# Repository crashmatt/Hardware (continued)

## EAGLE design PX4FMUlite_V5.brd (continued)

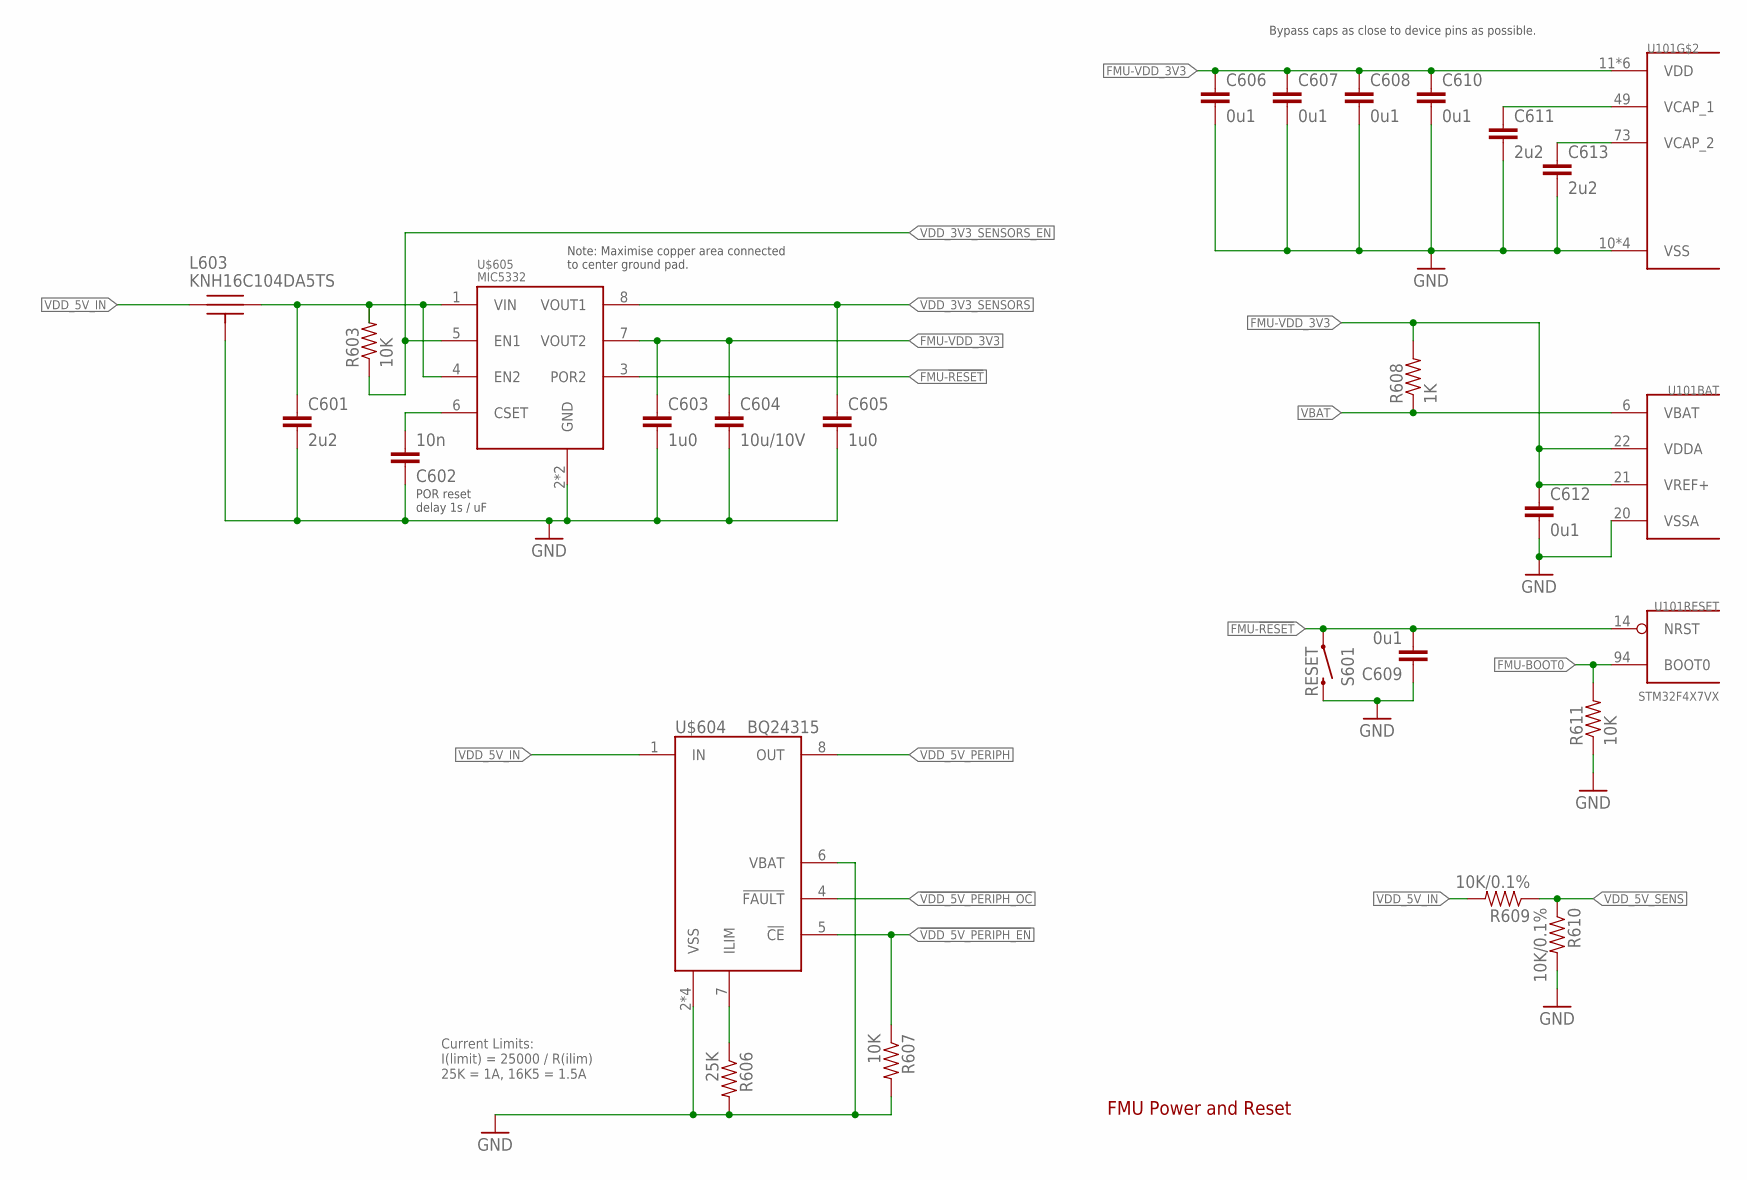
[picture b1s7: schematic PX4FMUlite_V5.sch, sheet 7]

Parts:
C601, C611, C613: 2u2; 0603-CAP; PARTNO C1608Y5V1C225Z
C602: 10n; 0402-CAP; PARTNO CC0402KRX7R7BB103
C603, C605: 1u0; 0603-CAP; PARTNO CC0603ZRY5V7BB105
C604: 10u/10V; 0805-CAP; PARTNO CC0805ZKY5V6BB106
C606, C607, C608, C609, C610, C612: 0u1; 0402-CAP; PARTNO CC0402ZRY5V7BB104
L603: KNH16C104DA5TS; KYOCERA-KNH16-DA; PARTNO KNH16C104DA5TS
R603, R607, R611: 10K; 0402-RES; PARTNO RC0402FR-0710KL
R606: 25K; 0402-RES; PARTNO RMCF0402FT25K5
R608: 1K; 0402-RES; PARTNO RC0402FR-071KL
R609, R610: 10K/0.1%; 0402-RES; PARTNO ERA-2AEB103X
S601: RESET; EVQP7J01K; PARTNO EVQP7J01K
U101: STM32F4X7VX; TQFP100; PARTNO STM32F427VI
U$604: BQ24315; QFN8-DSG; PARTNO BQ24315DSGR
U$605: MIC5332; MLF-8-EPAD; PARTNO MIC5332-SSYMT

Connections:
!VDD_5V_PERIPH_EN: R607.P$1 (1), U$604.5 (!CE); also elsewhere on the board
!VDD_5V_PERIPH_OC: U$604.4 (!FAULT); also elsewhere on the board
FMU-!RESET: C609.P$2 (2), S601.A1 (1), U101.14 (NRST), U$605.3 (POR2); also elsewhere on the board
FMU-BOOT0: R611.P$2 (2), U101.94 (BOOT0); also elsewhere on the board
FMU-VDD_3V3: C603.P$1 (1), C604.P$1 (1), C606.P$1 (1), C607.P$1 (1), C608.P$1 (1), C610.P$1 (1), C612.P$1 (1), R608.P$2 (2), U101.11 (VDD), U101.19 (VDD), U101.21 (VREF+), U101.22 (VDDA), U101.28 (VDD), U101.50 (VDD), U101.75 (VDD), U101.100 (VDD), U$605.7 (VOUT2); also elsewhere on the board
FMU-VDD_5V5: C601.P$1 (1), L603.P$2, R603.P$2 (2), U$605.1 (VIN), U$605.4 (EN2)
GNDX: C601.P$2 (2), C602.P$1 (1), C603.P$2 (2), C604.P$2 (2), C605.P$2 (2), C606.P$2 (2), C607.P$2 (2), C608.P$2 (2), C609.P$1 (1), C610.P$2 (2), C611.P$2 (2), C612.P$2 (2), C613.P$2 (2), L603.P$3, L603.P$4, L603.P$5, R606.P$2 (2), R607.P$2 (2), R610.P$2 (2), R611.P$1 (1), S601.B3 (2), U101.10 (VSS), U101.20 (VSSA), U101.27 (VSS), U101.74 (VSS), U101.99 (VSS), U$604.2 (VSS), U$604.6 (VBAT), U$604.GND (VSS), U$604.P$2 (VSS), U$604.P$3 (VSS), U$605.2 (GND), U$605.GND; also elsewhere on the board
unnamed: C613.P$1 (1), U101.73 (VCAP_2)
unnamed: C602.P$2 (2), U$605.6 (CSET)
unnamed: C611.P$1 (1), U101.49 (VCAP_1)
unnamed: R606.P$1 (1), U$604.7 (ILIM)
VBAT: R608.P$1 (1), U101.6 (VBAT)
VDD_3V3_SENSORS: C605.P$1 (1), U$605.8 (VOUT1); also elsewhere on the board
VDD_3V3_SENSORS_EN: R603.P$1 (1), U$605.5 (EN1); also elsewhere on the board
VDD_5V_IN: L603.P$1, R609.P$2 (2), U$604.1 (IN); also elsewhere on the board
VDD_5V_PERIPH: U$604.8 (OUT); also elsewhere on the board
VDD_5V_SENS: R609.P$1 (1), R610.P$1 (1); also elsewhere on the board

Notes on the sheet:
FMU Power and Reset
Bypass caps as close to device pins as possible.
Note: Maximise copper area connected to center ground pad.
POR reset delay 1s / uF
Current Limits: I(limit) = 25000 / R(ilim) 25K = 1A, 16K5 = 1.5A

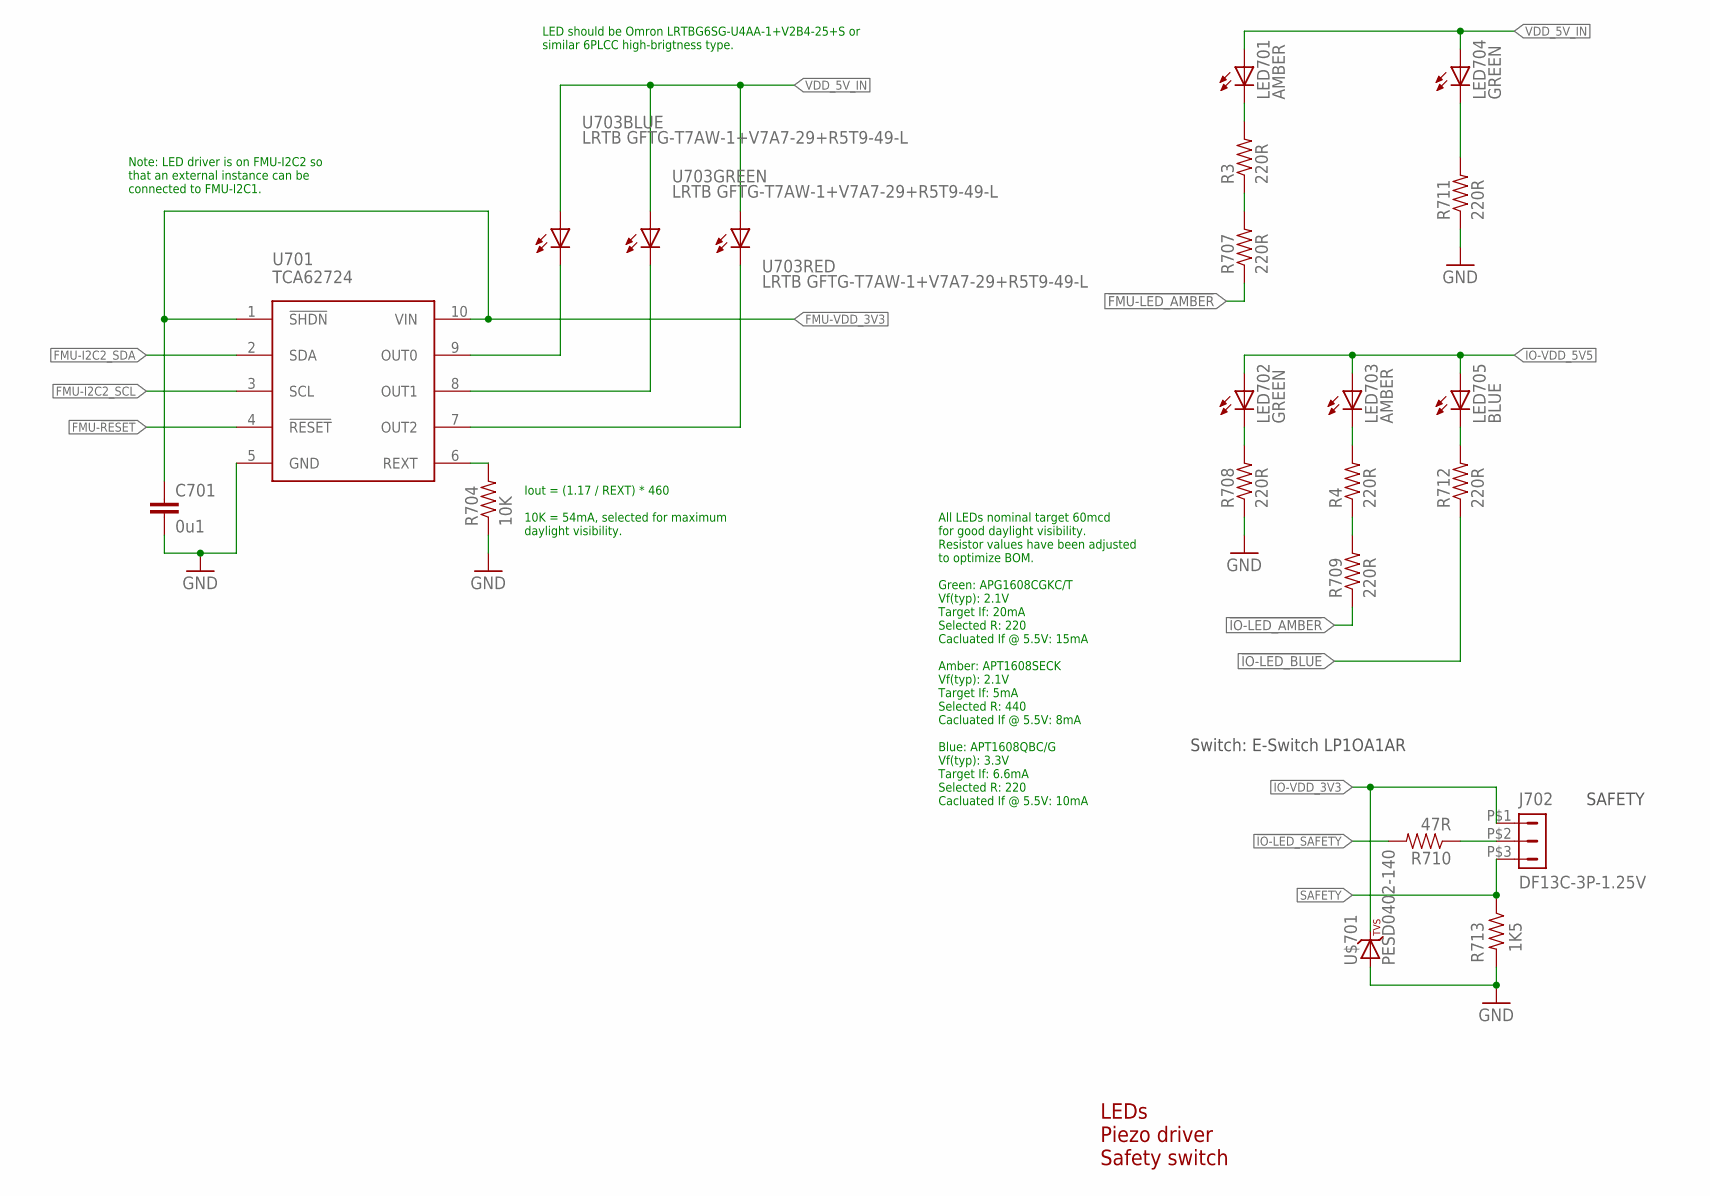
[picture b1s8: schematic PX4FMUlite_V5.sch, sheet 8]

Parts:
C701: 0u1; 0402-CAP; PARTNO CC0402ZRY5V7BB104
J702: DF13C-3P-1.25V; PARTNO DF13C-3P-1.25V(20)
LED701, LED703: AMBER; 0603-LED; PARTNO APTD1608SECK
LED702, LED704: GREEN; 0603-LED; PARTNO APTD1608CGCK
LED705: BLUE; 0603-LED; PARTNO APTD1608QBC/D
R3, R4, R707, R708, R709, R711, R712: 220R; 0402-RES; PARTNO RC0402FR-07220RL
R704: 10K; 0402-RES; PARTNO RC0402FR-0710KL
R710: 47R; 0402-RES; PARTNO RC0402JR-0747RL
R713: 1K5; 0402-RES; PARTNO RC0402FR-071K5L
U701: TCA62724FMG; SON10; PARTNO TCA62724FMG
U703: LRTB GFTG-T7AW-1+V7A7-29+R5T9-49-L; 6-PLCC; PARTNO LRTB GFTG-T7AW-1+V7A7-29+R5T9-49-L
U$701: PESD0402-140; 0402-TVS; PARTNO PESD0402-140

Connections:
!FMU-LED_AMBER: R707.P$1 (1); also elsewhere on the board
!IO-LED_AMBER: R709.P$1 (1)
!IO-LED_BLUE: R712.P$1 (1)
!IO-LED_SAFETY: R710.P$2 (2)
FMU-!RESET: U701.4 (!RESET); also elsewhere on the board
FMU-I2C2_SCL: U701.3 (SCL); also elsewhere on the board
FMU-I2C2_SDA: U701.2 (SDA); also elsewhere on the board
FMU-VDD_3V3: C701.P$1 (1), U701.1 (!SHDN), U701.10 (VIN); also elsewhere on the board
GNDX: C701.P$2 (2), R704.P$1 (1), R708.P$1 (1), R711.P$1 (1), R713.P$2 (2), U701.5 (GND), U$701.A; also elsewhere on the board
IO-VDD_3V3: J702.P$1 (1), U$701.C; also elsewhere on the board
IO-VDD_5V5: LED702.A, LED703.A, LED705.A; also elsewhere on the board
unnamed: LED704.C, R711.P$2 (2)
unnamed: LED705.C, R712.P$2 (2)
unnamed: R3.P$1 (1), R707.P$2 (2)
unnamed: LED701.C, R3.P$2 (2)
unnamed: LED702.C, R708.P$2 (2)
unnamed: R4.P$1 (1), R709.P$2 (2)
unnamed: LED703.C, R4.P$2 (2)
unnamed: J702.P$2 (2), R710.P$1 (1)
unnamed: R704.P$2 (2), U701.6 (REXT)
RGB_LED_3: U701.9 (OUT0), U703.C1 (C)
RGB_LED_4: U701.8 (OUT1), U703.C2 (C)
RGB_LED_14: U701.7 (OUT2), U703.C3 (C)
SAFETY: J702.P$3 (3), R713.P$1 (1)
VDD_5V_IN: LED701.A, LED704.A, U703.A1 (A), U703.A2 (A), U703.A3 (A); also elsewhere on the board

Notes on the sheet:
LEDs Piezo driver Safety switch
Switch: E-Switch LP1OA1AR
SAFETY
LED should be Omron LRTBG6SG-U4AA-1+V2B4-25+S or similar 6PLCC high-brigtness type.
Iout = (1.17 / REXT) * 460 10K = 54mA, selected for maximum daylight visibility.
Note: LED driver is on FMU-I2C2 so that an external instance can be connected to FMU-I2C1.
All LEDs nominal target 60mcd for good daylight visibility. Resistor values have been adjusted to optimize BOM. Green: APG1608CGKC/T Vf(typ): 2.1V Target If: 20mA Selected R: 220 Cacluated If @ 5.5V: 15mA Amber: APT1608SECK Vf(typ): 2.1V Target If: 5mA Selected R: 440 Cacluated If @ 5.5V: 8mA Blue: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

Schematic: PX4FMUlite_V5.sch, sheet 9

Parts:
J801: JST-ZH-3; JST-ZH-SMT-VERTICAL; PARTNO B3B-ZR-SM4-TF (LF)(SN)(P)
JX801: HEADER-3X1BOARDEDGE-SHORT; HEADER_3X01_SMD_H_BOARD_EDGE_SHORT
U$801: PESD0402-140; 0402-TVS; PARTNO PESD0402-140

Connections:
GNDX: J801.P$2, JX801.3 (GND), U$801.A; also elsewhere on the board
IO-USART1_RX: J801.P$3, JX801.2 (+5V)
IO-USART1_TX: JX801.1 (PPM); also elsewhere on the board
VDD_3V3_SPEKTRUM: J801.P$1, U$801.C; also elsewhere on the board

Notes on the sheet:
IO SoC Ports Spektrum/DSM port
IO_SERIAL1
Spektrum/DSM
Timer allocation: PA0: TIM2_CH1: IO-CH1 PA1: TIM2_CH2: IO-CH2 PB8: TIM4_CH3: IO-CH3 PB9: TIM4_CH4: IO-CH4 PA6: TIM3_CH1: IO-CH5 PA7: TIM3_CH2: IO-CH6 PB0: TIM3_CH3: IO-CH7 PB1: TIM3_CH4: IO-CH8 PA8: TIM1_CH1: PPM_IN PA11: TIM1_CH4: RSSI_IN

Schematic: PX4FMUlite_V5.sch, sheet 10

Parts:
C901, C902: 0u1; 0402-CAP; PARTNO CC0402ZRY5V7BB104
D1: MSS1P4-M3; MICROSMP; PARTNO MSS1P4-M3/89A
J901: HEADER-3X163X16RA; 3X16RA
L901: KNH16C104DA5TS; KYOCERA-KNH16-DA; PARTNO KNH16C104DA5TS
R901: 10K; 0402-RES; PARTNO RC0402FR-0710KL
R902, R903, R904, R909, R910, R911, R912, R913: 220R; 0402-RES; PARTNO RC0402FR-07220RL
R918, R919, R922: 10K/0.1%; 0402-RES; PARTNO ERA-2AEB103X
U901: TXS0108QFN20; QFN20-RGY; PARTNO TXS0108ERGYR
U903: 74LVC2G240; TSSOP8_SOT505-2; PARTNO 74LVC2G240DP,125
U$6, U$901, U$902: PESD0402-140; 0402-TVS; PARTNO PESD0402-140

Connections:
!SBUS_OUTPUT_EN: U903.7 (!2OE)
FMU-CH1: U901.7 (A6); also elsewhere on the board
FMU-CH1-PROT: J901.46, R913.P$2 (2)
FMU-CH2: U901.6 (A5); also elsewhere on the board
FMU-CH3: U901.5 (A4); also elsewhere on the board
FMU-CH4: U901.4 (A3); also elsewhere on the board
FMU-CH5: U901.3 (A2); also elsewhere on the board
FMU-CH6: U901.1 (A1); also elsewhere on the board
FMU-CH6-PROT: J901.31, R902.P$2 (2)
FMU-VDD_3V3: C902.P$1 (1), U901.2 (VCCA), U901.10 (OE), U901.19 (VCCB); also elsewhere on the board
GNDX: C901.P$2 (2), C902.P$2 (2), J901.3, J901.6, J901.9, J901.12, J901.15, J901.18, J901.21, J901.24, J901.27, J901.30, J901.33, J901.36, J901.39, J901.42, J901.45, J901.48, L901.P$3, L901.P$4, L901.P$5, R919.P$1 (1), U901.11 (GND), U903.1 (!1OE), U903.4 (GND), U$6.A, U$901.A, U$902.A; also elsewhere on the board
IO-VDD_3V3: C901.P$1 (1), U903.8 (VCC); also elsewhere on the board
IO-VDD_5V5: J901.2; also elsewhere on the board
unnamed: R918.P$2 (2), R922.P$1 (1)
unnamed: R901.P$2 (2), R910.P$1 (1), U903.3 (2Y), U$902.C
unnamed: R902.P$1 (1), U901.20 (B1)
unnamed: R911.P$1 (1), U901.18 (B2)
unnamed: R903.P$1 (1), U901.17 (B3)
unnamed: R912.P$1 (1), U901.16 (B4)
unnamed: R904.P$1 (1), U901.15 (B5)
unnamed: R913.P$1 (1), U901.14 (B6)
unnamed: J901.34, R911.P$2 (2)
unnamed: J901.37, R903.P$2 (2)
unnamed: J901.40, R912.P$2 (2)
unnamed: J901.43, R904.P$2 (2)
unnamed: J901.4, R910.P$2 (2)
unnamed: D1.CATHODE (C), L901.P$1, U$6.C
PPM-SBUS-PROT: J901.1, R909.P$2 (2)
PPM_INPUT: R909.P$1 (1), U903.2 (1A), U$901.C
RSSI_IN: R901.P$1 (1)
SBUS_INPUT: U903.6 (1Y)
SBUS_OUTPUT: U903.5 (2A)
VDD_SERVO: D1.ANODE (A), J901.5, J901.8, J901.11, J901.14, J901.17, J901.20, J901.23, J901.26, J901.29, J901.32, J901.35, J901.38, J901.41, J901.44, J901.47, R922.P$2 (2)
VDD_SERVO_IN: L901.P$2; also elsewhere on the board
VDD_SERVO_SENS: R918.P$1 (1), R919.P$2 (2)

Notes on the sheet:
Servo Header S.Bus interface
S.Bus in/out
Servo outputs
XXX TEST effect of 5V, 7V applied to PWM input pins. Do we need something to dump this to ground?

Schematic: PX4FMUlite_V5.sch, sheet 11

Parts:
C1001, C1003, C1004: 1u0; 0603-CAP; PARTNO CC0603ZRY5V7BB105
C1002: 10n; 0402-CAP; PARTNO CC0402KRX7R7BB103
D1001: PMEG2005CT; SOT23-3; PARTNO PMEG2005CT
F2: 0ZCA0035FF2G; PTC-1206; PARTNO 0ZCA0035FF2G
R1001: 100K; 0402-RES; PARTNO RC0402FR-07100KL
R1002: 10K; 0402-RES; PARTNO RC0402FR-0710KL
U$1001: BQ24313; QFN8-DSG; PARTNO BQ24313DSGT
U$1002: MIC5332; MLF-8-EPAD; PARTNO MIC5332-SSYMT

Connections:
GNDX: C1001.P$2 (2), C1002.P$2 (2), C1003.P$2 (2), C1004.P$2 (2), R1001.P$1 (1), R1002.P$1 (1), U$1001.2 (VSS), U$1001.5 (!CE), U$1001.6 (VBAT), U$1001.GND (VSS), U$1001.P$2 (VSS), U$1001.P$3 (VSS), U$1002.2 (GND), U$1002.GND; also elsewhere on the board
IO-!RESET: U$1002.3 (POR2)
IO-!VDD_SERVO_IN_FAULT: U$1001.4 (!FAULT)
IO-VDD_3V3: C1004.P$1 (1), U$1002.7 (VOUT2); also elsewhere on the board
IO-VDD_5V5: C1001.P$1 (1), D1001.3 (CC), U$1002.1 (VIN), U$1002.4 (EN2); also elsewhere on the board
unnamed: D1001.2 (A2), U$1001.8 (OUT)
unnamed: R1001.P$2 (2), U$1001.7 (ILIM)
unnamed: D1001.1 (A1), F2.2
unnamed: C1002.P$1 (1), U$1002.6 (CSET)
VDD_3V3_SPEKTRUM: C1003.P$1 (1), U$1002.8 (VOUT1); also elsewhere on the board
VDD_3V3_SPEKTRUM_EN: R1002.P$2 (2), U$1002.5 (EN1)
VDD_5V_IN: F2.1; also elsewhere on the board
VDD_SERVO_IN: U$1001.1 (IN); also elsewhere on the board

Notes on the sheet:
Dual supply from servo rail and FMU 5V rail
Current limit = 25 / Rilim (current in A, R in kOhms) 100K = 250mA
IO Power Supply
Reset output 1s / uF 10n = 10ms delay from power good to reset de-asserted.
Output voltage limited to 5.5V for input voltages up to 10.5V; output switches off at higher input voltages.

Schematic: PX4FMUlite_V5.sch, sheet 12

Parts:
ADC_PR: PAD.04; PAD.04X.04; PARTNO *
CAN_H: PAD.04; PAD.04X.04; PARTNO *
CAN_L: PAD.04; PAD.04X.04; PARTNO *
FMU-BOOT1101: PAD.04; PAD.04X.04; PARTNO *
GND, GND.: PAD.04; PAD.04X.04; PARTNO *
IO-BOOT1101: PAD.04; PAD.04X.04; PARTNO *
JP1, JP2: FIDUCIAL1.5X3; FIDUCIAL-1.5X3; PARTNO *
M3_MOUNT1101, M3_MOUNT1102, M3_MOUNT1103, M3_MOUNT1104: MOUNT-HOLE3.1MM; MOUNT-HOLE3.1; PARTNO *
OSHW_LOGO: OSHW-LOGOS; OSHW-LOGO-S; PARTNO *
S1RX, S1TX, S2RX, S2TX, S3RX, S3TX, S4RX, S4TX, S5_RX, S5_TX: PAD.04; PAD.04X.04; PARTNO *
VDDA_3V1101: PAD.04; PAD.04X.04; PARTNO *
VDD_3V1101, VDD_5V_BRICK: PAD.04; PAD.04X.04; PARTNO *

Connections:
CAN_H: CAN_H.P$1; also elsewhere on the board
CAN_L: CAN_L.P$1; also elsewhere on the board
FMU-BOOT0: FMU-BOOT1101.P$1; also elsewhere on the board
FMU-VDD_3V3: VDD_3V1101.P$1; also elsewhere on the board
GNDX: GND.P$1, GND..P$1; also elsewhere on the board
IO-BOOT0: IO-BOOT1101.P$1
PRESSURE_SENS_IN: ADC_PR.P$1
SERIAL1_RX: S1RX.P$1; also elsewhere on the board
SERIAL1_TX: S1TX.P$1; also elsewhere on the board
SERIAL2_RX: S2RX.P$1; also elsewhere on the board
SERIAL2_TX: S2TX.P$1; also elsewhere on the board
SERIAL3_RX: S3RX.P$1; also elsewhere on the board
SERIAL3_TX: S3TX.P$1; also elsewhere on the board
SERIAL4_RX: S4RX.P$1; also elsewhere on the board
SERIAL4_TX: S4TX.P$1; also elsewhere on the board
SERIAL5_RX: S5_RX.P$1; also elsewhere on the board
SERIAL5_TX: S5_TX.P$1; also elsewhere on the board
VDD_3V3_SENSORS: VDDA_3V1101.P$1; also elsewhere on the board
VDD_5V_BRICK: VDD_5V_BRICK.P$1; also elsewhere on the board

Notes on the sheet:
Mounting holes to suit M3 fastener
and Richco R908 series spacer.
Use R908-5 spacers to stack with
other PX4 series boards (7.95 mm).
Production Testing Pads
Test and Fiducials
Minimum drill: 0.3 mm
Minimum trace width (use mm for traces): 0.15 mm
Minimum copper distance (all signals): 0.15 mm
Dimension / hole minimum distance: 0.2 mm
Layout grid: 4 mil, part grid: 4 mil. Dimensions / hole positions: 0.5 mm
Board: FR4 black, 1.0 mm. Solder stop on vias < 0.6 mm.
Signoff rules: Footprint checked, pinmap checked, schematic checked, cross-references to other pages checked.
Routing: 1: general/escape 2: ground 3: horizontal 4: vertical 5: power 6: general/escape
Fiducials for machine vision alignment.

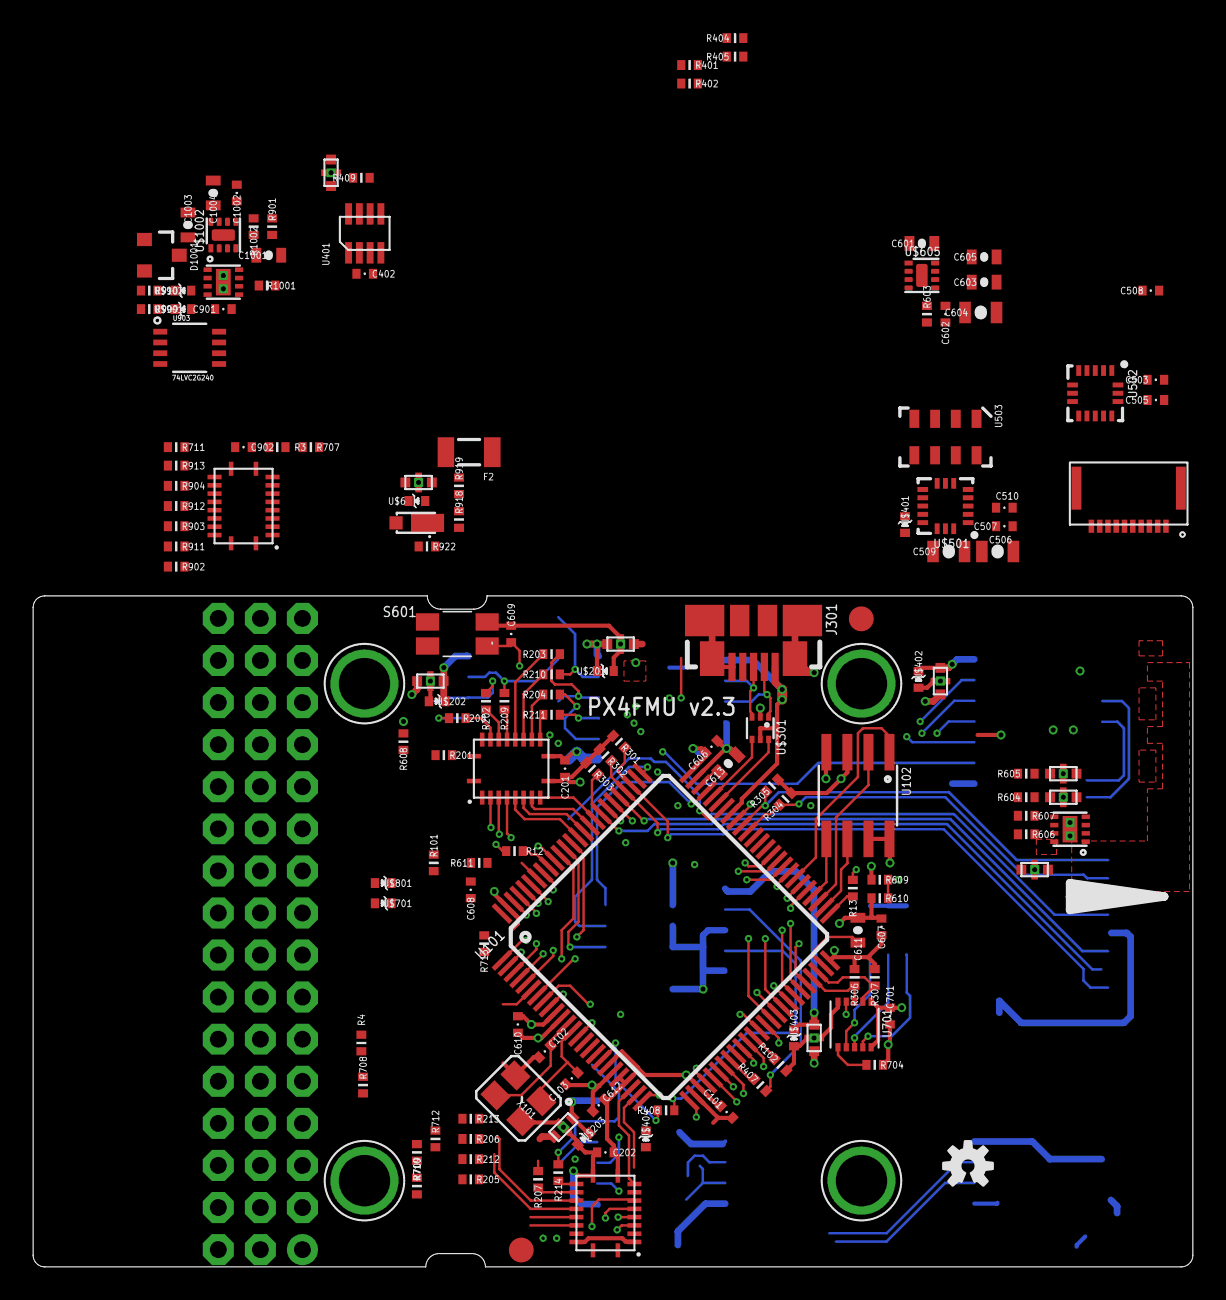
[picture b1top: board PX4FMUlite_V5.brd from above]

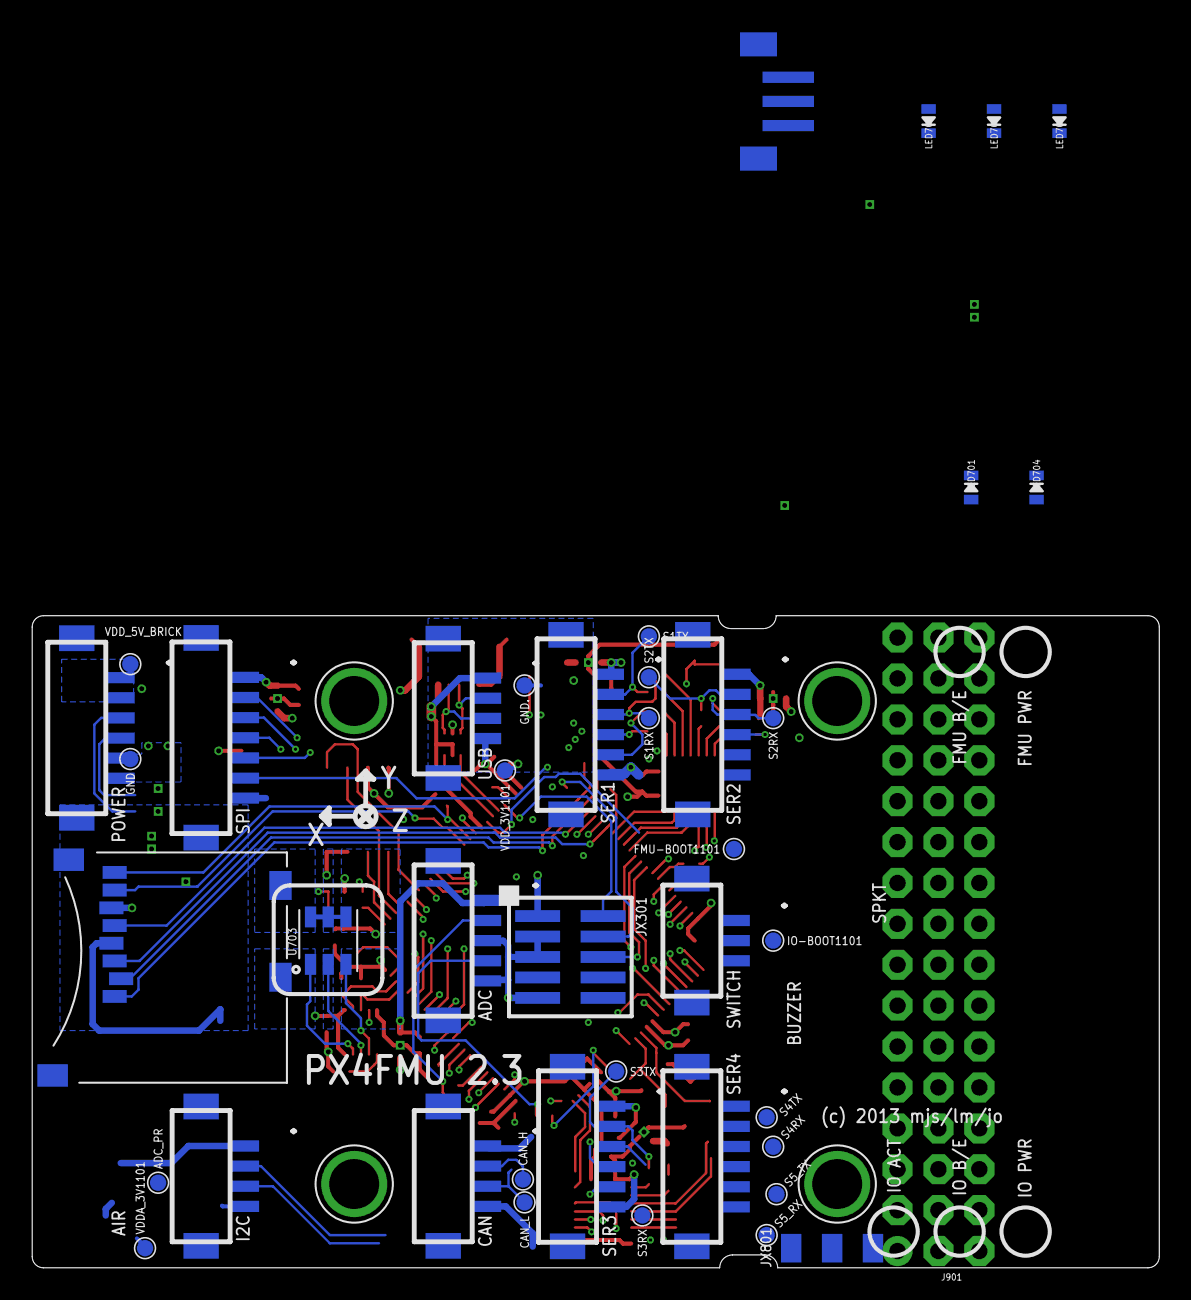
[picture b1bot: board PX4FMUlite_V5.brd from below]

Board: 6 copper layers, 70.0 x 40.5 mm, 192 parts (42 on the bottom side), 180 nets.
